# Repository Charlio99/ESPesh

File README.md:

# ESPesh

ESPesh is a super tiny board designed for IoT applications.
My plan is to use it as a BLE Mesh for IoT sensors and switches, because with BLE the power consumption is less than 1mA.

# Features

  - ESP32-PICO-D4
  - Low power design (LDO, removed unnecessary components)
  - Only one inch PCB
  - USB C (only for power, not programming)
  - LiPO battery (with charger and voltage protections)
  - Some GPIOs exposed (I2C included)

### BOM

I mainly use JLCPCB and LCSC for PCB and components.

| Component | Quantity | Link | Price |
| ------ | ------ | ------ | ------ |
| ESP32-PICO-D4 | 1 | https://lcsc.com/product-detail/Others_Espressif-Systems-ESP32-PICO-D4_C193707.html | $4.34 |
| PRO-OB-440 | 1 | https://www.digikey.es/product-detail/es/proant-ab/PRO-OB-440/1532-1001-1-ND/4895684 | $0.95 |
| LIR2450 | 1 | https://es.aliexpress.com/item/32853897751.html | $2.76 |
| 0.1uF | 3 | https://lcsc.com/product-detail/Multilayer-Ceramic-Capacitors-MLCC-SMD-SMT_SAMSUNG_CL10B104KA8NNNC_100nF-104-10-25V_C1590.html | $0.29 |
| 2.7pF | 1 | https://lcsc.com/product-detail/Multilayer-Ceramic-Capacitors-MLCC-SMD-SMT_SAMSUNG_CL10C2R7CB8NNNC_2-7pF-2R7-0-25pF-50V_C16149.html | $0.61 |
| 4.7pF | 1 | https://lcsc.com/product-detail/Multilayer-Ceramic-Capacitors-MLCC-SMD-SMT_SAMSUNG_CL10C4R7CB8NNNC_4-7pF-4R7-0-25pF-50V_C57140.html | $0.405 |
| 10uF Tantalum | 2 | https://lcsc.com/product-detail/Tantalum-Capacitors_AVX_TAJA106K010RNJ_10uF-106-10-10V_C7177.html | $0.2386 |
| 10uF | 1 | https://lcsc.com/product-detail/Multilayer-Ceramic-Capacitors-MLCC-SMD-SMT_SAMSUNG_CL10A106KP8NNNC_10uF-106-10-10V_C19702.html | $0.52 |
| LED 0603 | 1 | https://lcsc.com/product-detail/Light-Emitting-Diodes-LED_Red-LED-SMDLED-80-100mcd_C84263.html | $0.64 |
| SK6805 | 1 | https://es.aliexpress.com/item/32903030496.html | $3.23 |
| MBR0520 | 1 | https://lcsc.com/product-detail/Schottky-Barrier-Diodes-SBD_Changjiang-Electronics-Tech-CJ-MBR0520_C77335.html | $0.56 |
| FDN340P | 1 | https://lcsc.com/product-detail/MOSFET_ON-Semicon_FDN340P_ON-Semicon-ON-FDN340P_C75469.html | $0.1241 |
| 1.6nH | 1 | https://lcsc.com/product-detail/Others_GOOGLL-GGW0603UC1N6KGT_C343064.html | $0.0310 |
| 10K | 2 | https://lcsc.com/product-detail/Chip-Resistor-Surface-Mount_Uniroyal-Elec-0603WAF1002T5E_C25804.html | $0.1 |
| 6.8K | 2 | https://lcsc.com/product-detail/Chip-Resistor-Surface-Mount_Uniroyal-Elec-0603WAF6801T5E_C23212.html | $0.1 |
| 2K | 1 | https://lcsc.com/product-detail/Chip-Resistor-Surface-Mount_Uniroyal-Elec-0603WAF2001T5E_C22975.html | $0.1 |
| 5K1 | 2 | https://lcsc.com/product-detail/Chip-Resistor-Surface-Mount_Uniroyal-Elec-0603WAF5101T5E_C23186.html | $0.1 |
| 43K | 1 | https://lcsc.com/product-detail/Chip-Resistor-Surface-Mount_Uniroyal-Elec-0603WAF4302T5E_C23172.html | $0.11 |
| 100R | 1 | https://lcsc.com/product-detail/Chip-Resistor-Surface-Mount_Uniroyal-Elec-0603WAF1000T5E_C22775.html | $0.11 |
| 100K | 1 | https://lcsc.com/product-detail/Chip-Resistor-Surface-Mount_Uniroyal-Elec-0603WAF1003T5E_C25803.html | $0.1 |
| SPX3819M5-L-3-3 | 1 | https://lcsc.com/product-detail/Low-Dropout-Regulators-LDO_EXAR_SPX3819M5-L-3-3-TR_SPX3819M5-L-3-3-TR_C9055.html | $0.1225 |
| SL4054ST25P | 1 | https://lcsc.com/product-detail/Others_TECHFUSE-SL4054ST25P_C258510.html | $0.509 |
| XB6566H0 | 1 | https://lcsc.com/product-detail/Others_XB6566H0_C190847.html | $0.1734 |
| HDC1080 | 1 | https://lcsc.com/product-detail/Humidity-Moisture-Sensors_TI_HDC1080DMBR_HDC1080DMBR_C82227.html | $1.1216 |
| HRO-TYPE-C-31-M-12 | 1 | https://lcsc.com/product-detail/USB-Type-C_Korean-Hroparts-Elec-TYPE-C-31-M-12_C165948.html | $0.3882 |
| | | **TOTAL** | **$17.7334**|

Take in account that some components must be ordered in larger batches that the quantity needed (for example: SK6805: we need only one, but min order is 10).

### Todos

 - Wiki
 - Test the board
 - Sell it on Tindie so I can keep developing such tiny boards

### License

Creative Commons Attribution-NonCommercial-ShareAlike 4.0 International Public License

**Open Source, Hell Yeah!**

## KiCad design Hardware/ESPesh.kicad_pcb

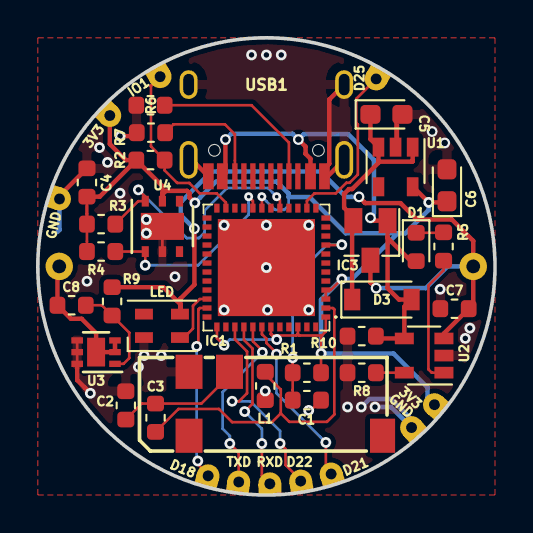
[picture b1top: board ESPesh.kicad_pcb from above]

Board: 2 copper layers, 25.4 x 25.4 mm, 42 parts (1 on the bottom side), 25 nets.

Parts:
3V3, 3V3#2: Conn_01x01; RoundPadPassthrough
ANT1: PRO-OB-440; PRO-OB-440_1
BATT1: LIR2450
C1, C4, C8: 0.1uF; C_0603_1608Metric
C2: 2.7pF; C_0603_1608Metric
C3: 4.7pF; C_0603_1608Metric
C5, C6: 10uF; CP_EIA-2012-12_Kemet-R
C7: 10uF; C_0603_1608Metric
D1: LED; LED_0603_1608Metric
D3: MBR0520; D_SOD-123
D18, D21, D22, D25: Conn_01x01; RoundPadPassthrough
GND: Conn_01x01; RoundPadPassthrough
GND#2: Conn_01x01; RoundPadPassthrough
IC1: ESP32-PICO-D4; ESP32PICOD4
IC3: FDN340P; SuperSOT-3
IO1: Conn_01x01; RoundPadPassthrough
L1: 1.6nH; L_0603_1608Metric
LED: SK6805; LED_SK6805_PLCC4_2.4x2.7mm_P1.3mm
R1, R2: 10K; R_0603_1608Metric
R3, R4: 6.8K; R_0603_1608Metric
R5: 2K; R_0603_1608Metric
R6, R7: 5K1; R_0603_1608Metric
R8: 43K; R_0603_1608Metric
R9: 100; R_0603_1608Metric
R10: 100K; R_0603_1608Metric
RXD: Conn_01x01; RoundPadPassthrough
TXD: Conn_01x01; RoundPadPassthrough
U1: SPX3819M5-L-3-3; SOT-23-5
U2: SL4054ST25P; SOT-23-5
U3: XB6566H0; DFN-6-1EP_2x2mm_P0.65mm_EP1x1.6mm
U4: HDC1080; Texas_PWSON-N6
USB1: HRO-TYPE-C-31-M-12; HRO-TYPE-C-31-M-12-Assembly

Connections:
+3V3: 3V3.1, 3V3#2.1, C4.2, C6.1, IC1.1, IC1.3, IC1.4, IC1.19, IC1.37, IC1.43, IC1.46, R1.2, R2.1, R3.1, R4.1, U1.5, U4.5
+BATT: BATT1.1, C7.1, IC3.1, LED.4, R9.2, U2.3
-BATT: BATT1.2, C8.2, U3.2, U3.3, U3.7
/EN: C1.1, IC1.9, R1.1
/IO0: IC1.23, IO1.1, R2.2
/IO18: D18.1, IC1.35
/IO21: D21.1, IC1.42
/IO22: D22.1, IC1.39
/IO25: D25.1, IC1.14
/LED: IC1.34, LED.3
/RXD: IC1.40, RXD.1
/SCL: IC1.17, R3.2, U4.6
/SDA: IC1.20, R4.2, U4.1
/TXD: IC1.41, TXD.1
GND: ANT1.1, C1.2, C2.2, C4.1, C5.2, C6.2, C7.2, GND.1, GND#2.1, IC1.49, L1.1, LED.2, R6.2, R7.2, R8.1, R10.2, U1.2, U2.2, U3.4, U3.5, U3.6, U4.2, U4.7, USB1.1, USB1.12, USB1.13
unnamed: ANT1.2, C2.1, C3.1
unnamed: C3.2, IC1.2, L1.2
unnamed: C8.1, R9.1, U3.1
unnamed: D1.1, R5.1
unnamed: R5.2, U2.1
unnamed: R6.1, USB1.4
unnamed: R7.1, USB1.10
unnamed: R8.2, U2.5
VCC: D1.2, D3.2, IC3.2, R10.1, U2.4, USB1.2, USB1.11
VDD: C5.1, D3.1, IC3.3, U1.1, U1.3

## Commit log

2019-05-07 First revision uploaded, NOT TESTED!
2019-05-07 Added PCB images
2019-05-07 Added GND pad
2019-05-07 Updated top PCB image
2019-05-07 rev0.2: fixed ESP32 footprint missmatch
2019-05-08 rev0.3 and panelized gerbers
2019-05-08 Updated image
2019-06-04 #1 Minor fixes and rev0.3 tested (antenna not tested yet)
2019-06-04 Now using the proper license for the hardware

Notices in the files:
README.md:
License: CC-BY-NC-SA-4.0
